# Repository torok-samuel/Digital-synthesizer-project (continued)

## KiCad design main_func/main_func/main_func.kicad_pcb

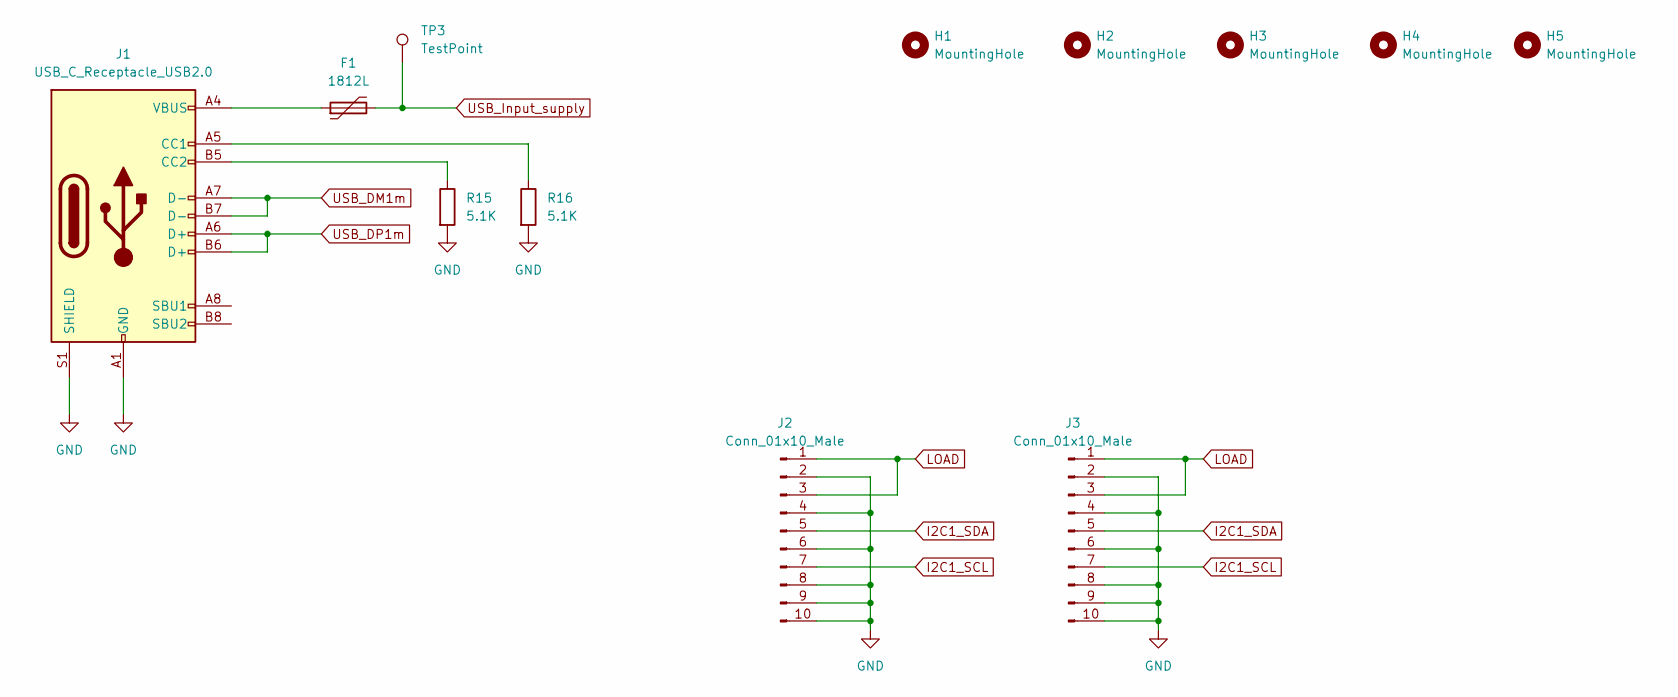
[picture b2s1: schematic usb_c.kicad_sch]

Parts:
F1: 1812L; FUSM4632X200N
H1, H2, H3, H4, H5: MountingHole; MountingHole_3.2mm_M3_Pad_Via
J1: USB_C_Receptacle_USB2.0; USB_C_Receptacle_HRO_TYPE-C-31-M-12
J2, J3: Conn_01x10_Male; IDC-Header_2x05_P2.54mm_Horizontal
R15, R16: 5.1K; R_0805_2012Metric_Pad1.20x1.40mm_HandSolder
TP3: TestPoint; TestPoint_Keystone_5010-5014_Multipurpose

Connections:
GND: J1.A1 (GND), J1.A12 (GND), J1.B1 (GND), J1.B12 (GND), J1.S1 (SHIELD), J2.2, J2.4, J2.6, J2.8, J2.9, J2.10, J3.2, J3.4, J3.6, J3.8, J3.9, J3.10, R15.2, R16.2; also elsewhere on the board
I2C1_SCL: J2.7, J3.7; also elsewhere on the board
I2C1_SDA: J2.5, J3.5; also elsewhere on the board
LOAD: J2.1, J2.3, J3.1, J3.3; also elsewhere on the board
unnamed: F1.1, J1.A4 (VBUS), J1.A9 (VBUS), J1.B4 (VBUS), J1.B9 (VBUS)
unnamed: J1.A5 (CC1), R16.1
unnamed: J1.B5 (CC2), R15.1
USB_DM1m: J1.A7 (D-), J1.B7 (D-); also elsewhere on the board
USB_DP1m: J1.A6 (D+), J1.B6 (D+); also elsewhere on the board
USB_Input_supply: F1.2, TP3.1; also elsewhere on the board

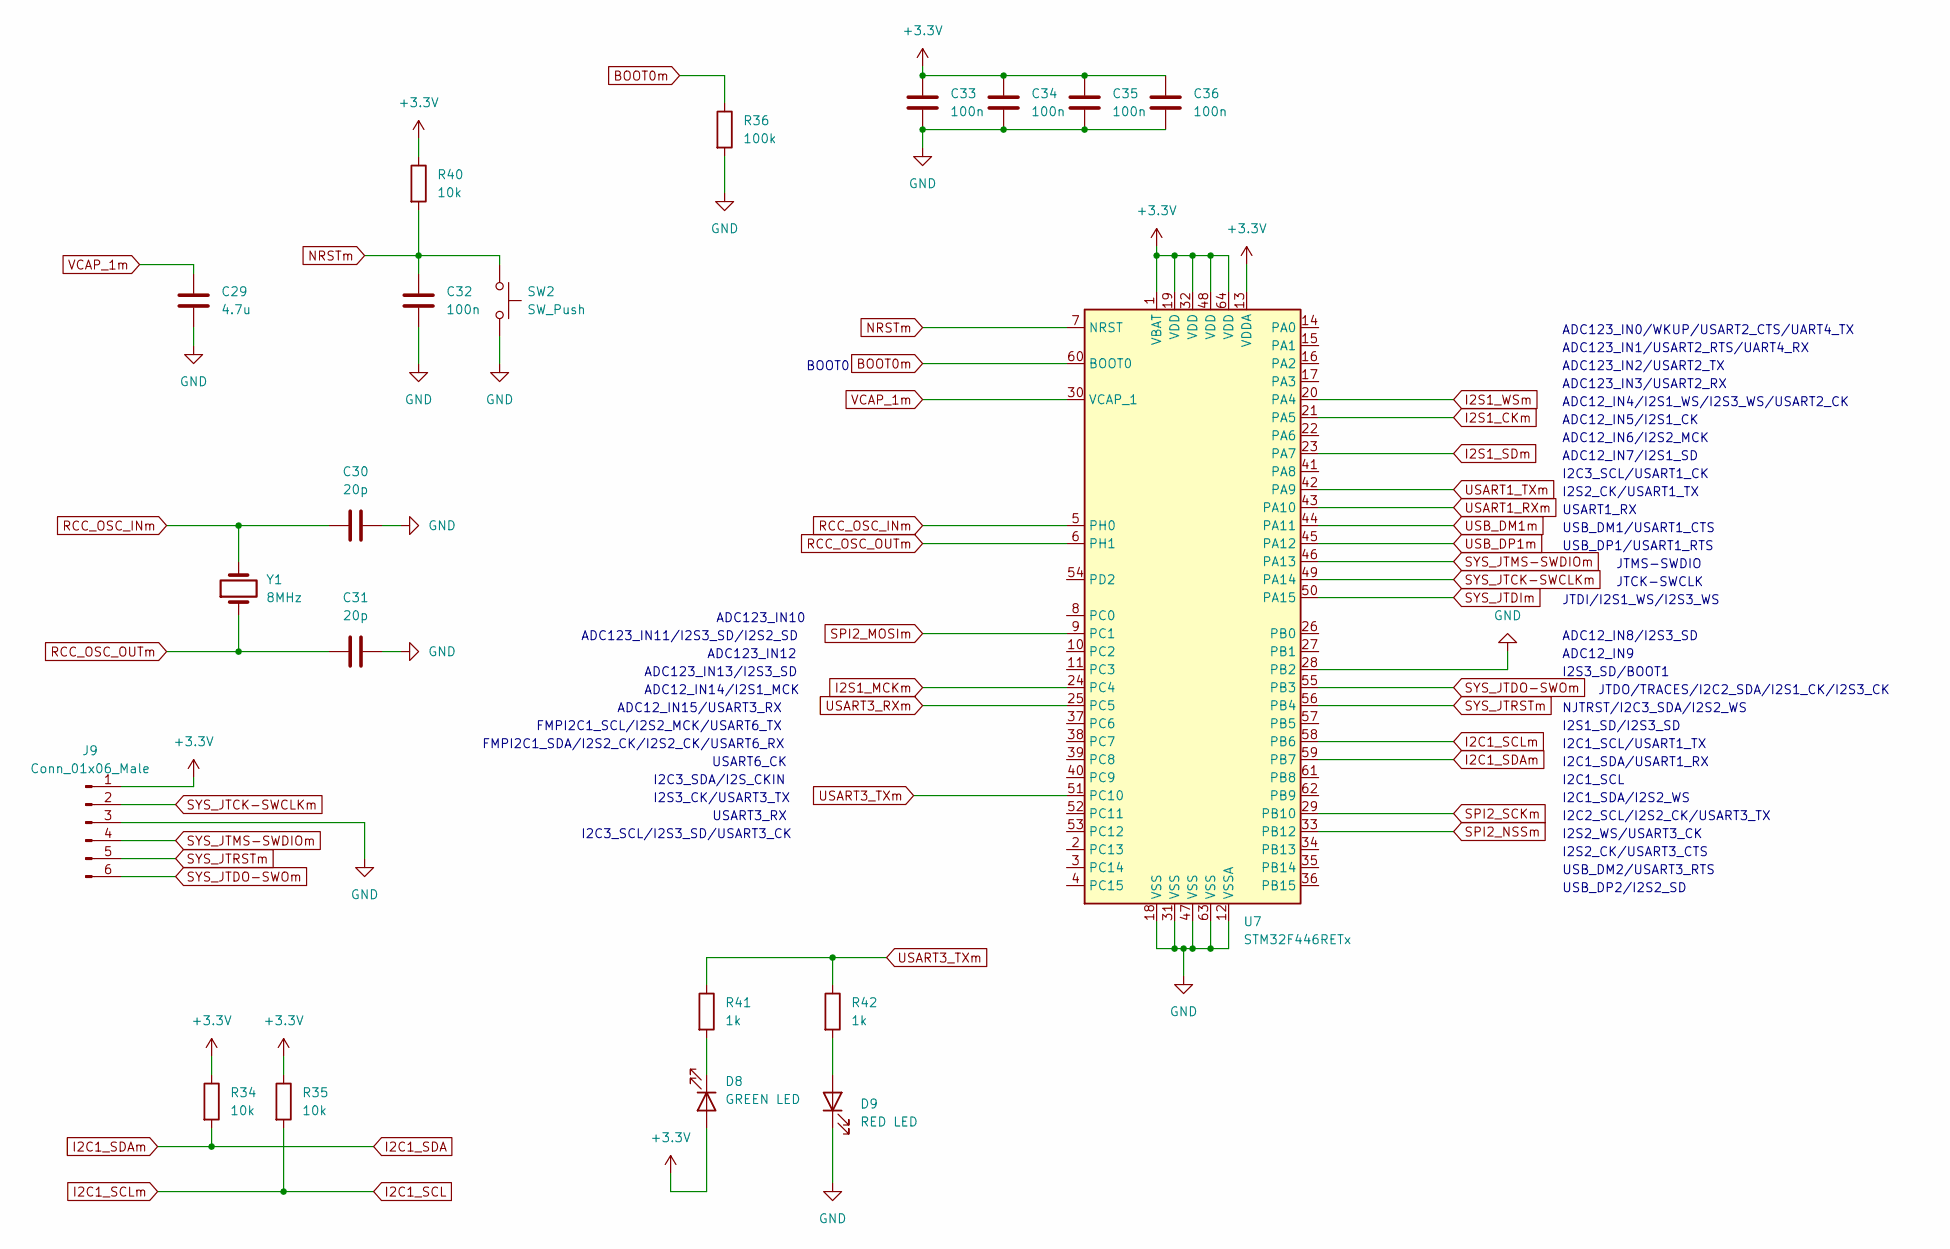
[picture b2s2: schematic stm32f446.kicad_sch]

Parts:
C29: 4.7u; C_0805_2012Metric_Pad1.18x1.45mm_HandSolder
C30, C31: 20p; C_0805_2012Metric_Pad1.18x1.45mm_HandSolder
C32, C33, C34, C35, C36: 100n; C_0805_2012Metric_Pad1.18x1.45mm_HandSolder
D8: GREEN LED; LED_0805_2012Metric_Pad1.15x1.40mm_HandSolder
D9: RED LED; LED_0805_2012Metric_Pad1.15x1.40mm_HandSolder
J9: Conn_01x06_Male; PinSocket_1x06_P2.54mm_Horizontal
R34, R35, R40: 10k; R_0805_2012Metric_Pad1.20x1.40mm_HandSolder
R36: 100k; R_0805_2012Metric_Pad1.20x1.40mm_HandSolder
R41, R42: 1k; R_0805_2012Metric_Pad1.20x1.40mm_HandSolder
SW2: SW_Push; ROCPU Switches TP10721645
U7: STM32F446RETx; LQFP-64_10x10mm_P0.5mm
Y1: 8MHz; Crystal_SMD_HC49-SD_HandSoldering

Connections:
+3V3: C33.1, C34.1, C35.1, C36.1, D8.2 (A), J9.1, R34.1, R35.1, R40.1, U7.1 (VBAT), U7.13 (VDDA), U7.19 (VDD), U7.32 (VDD), U7.48 (VDD), U7.64 (VDD); also elsewhere on the board
BCLKda: U7.21 (PA5); also elsewhere on the board
BOOT0m: R36.1, U7.60 (BOOT0)
DATAda: U7.23 (PA7); also elsewhere on the board
GND: C29.2, C30.2, C31.2, C32.2, C33.2, C34.2, C35.2, C36.2, D9.1 (K), J9.3, R36.2, SW2.2, U7.12 (VSSA), U7.18 (VSS), U7.28 (PB2), U7.31 (VSS), U7.47 (VSS), U7.63 (VSS); also elsewhere on the board
I2C1_SCL: R35.2, U7.58 (PB6); also elsewhere on the board
I2C1_SDA: R34.2, U7.59 (PB7); also elsewhere on the board
I2S1_MCKm: U7.24 (PC4); also elsewhere on the board
I2S1_WSm: U7.20 (PA4); also elsewhere on the board
MCda: U7.29 (PB10); also elsewhere on the board
MDda: U7.9 (PC1); also elsewhere on the board
MLda: U7.33 (PB12); also elsewhere on the board
NRSTm: C32.1, R40.2, SW2.1, U7.7 (NRST)
unnamed: D8.1 (K), R41.2
unnamed: D9.2 (A), R42.2
RCC_OSC_INm: C30.1, U7.5 (PH0), Y1.2
RCC_OSC_OUTm: C31.1, U7.6 (PH1), Y1.1
SYS_JTCK-SWCLKm: J9.2, U7.49 (PA14)
SYS_JTDIm: U7.50 (PA15)
SYS_JTDO-SWOm: J9.6, U7.55 (PB3)
SYS_JTMS-SWDIOm: J9.4, U7.46 (PA13)
SYS_JTRSTm: J9.5, U7.56 (PB4)
USART1_RXm: U7.43 (PA10); also elsewhere on the board
USART1_TXm: U7.42 (PA9); also elsewhere on the board
USART3_RXm: U7.25 (PC5)
USART3_TXm: R41.1, R42.1, U7.51 (PC10)
USB_DM1m: U7.44 (PA11); also elsewhere on the board
USB_DP1m: U7.45 (PA12); also elsewhere on the board
VCAP_1m: C29.1, U7.30 (VCAP_1)

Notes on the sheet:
ADC123_IN3/USART2_RX
I2S2_CK/USART3_CTS
FMPI2C1_SDA/I2S2_CK/I2S2_CK/USART6_RX
ADC12_IN4/I2S1_WS/I2S3_WS/USART2_CK
USB_DP2/I2S2_SD
I2C1_SCL
I2C1_SDA/USART1_RX
ADC12_IN7/I2S1_SD
ADC123_IN12
USART1_RX
FMPI2C1_SCL/I2S2_MCK/USART6_TX
I2C3_SDA/I2S_CKIN
I2C1_SCL/USART1_TX
USART6_CK
ADC123_IN0/WKUP/USART2_CTS/UART4_TX
I2S2_WS/USART3_CK
JTCK-SWCLK
JTMS-SWDIO
I2C3_SCL/USART1_CK
ADC123_IN10
NJTRST/I2C3_SDA/I2S2_WS
ADC123_IN2/USART2_TX
USB_DM1/USART1_CTS
I2C1_SDA/I2S2_WS
BOOT0
USART3_RX
ADC12_IN5/I2S1_CK
ADC12_IN14/I2S1_MCK
ADC123_IN13/I2S3_SD
ADC12_IN15/USART3_RX
I2C3_SCL/I2S3_SD/USART3_CK
ADC12_IN8/I2S3_SD
I2C2_SCL/I2S2_CK/USART3_TX
USB_DM2/USART3_RTS
ADC12_IN9
I2S3_CK/USART3_TX
ADC123_IN1/USART2_RTS/UART4_RX
JTDO/TRACES/I2C2_SDA/I2S1_CK/I2S3_CK
I2S1_SD/I2S3_SD
I2S3_SD/BOOT1

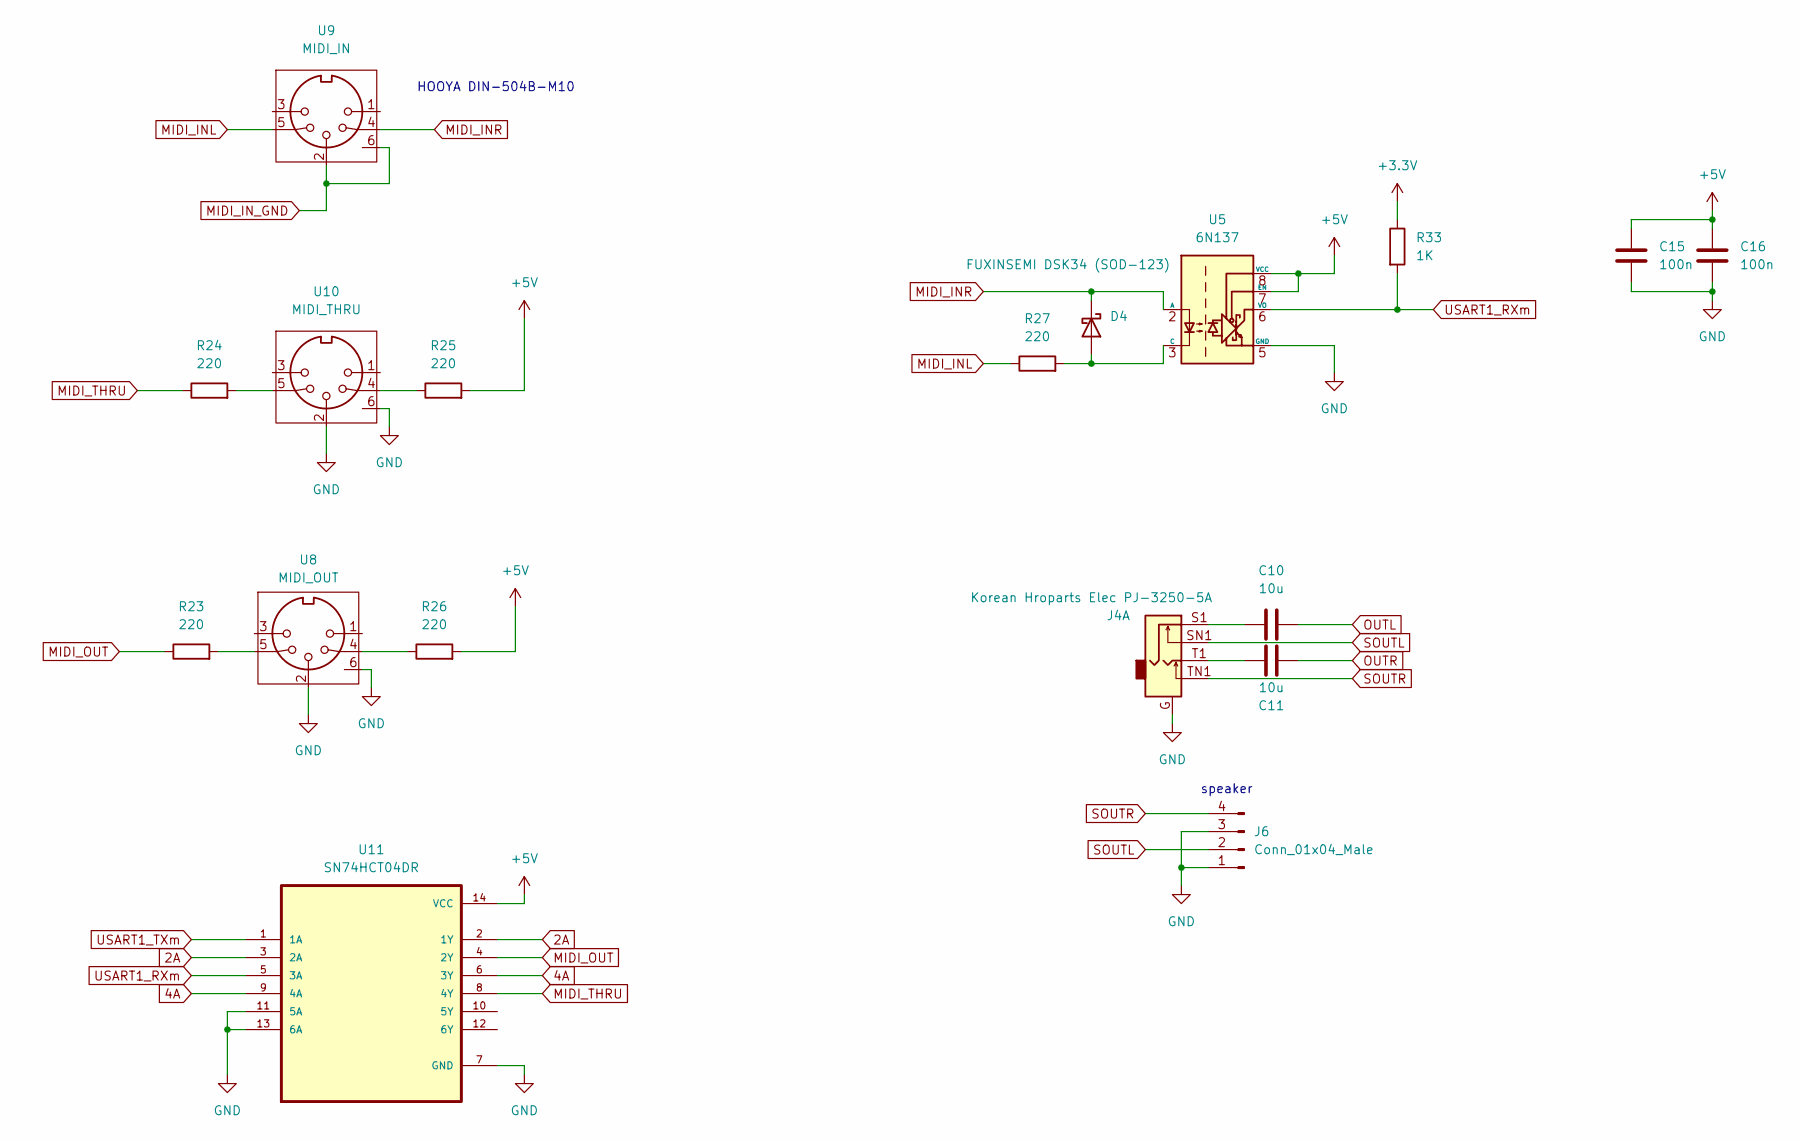
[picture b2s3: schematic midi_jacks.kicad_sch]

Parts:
C10, C11: 10u; C_Rect_L33.0mm_W15.0mm_P27.50mm_MKS4
C15, C16: 100n; C_0805_2012Metric_Pad1.18x1.45mm_HandSolder
D4: FUXINSEMI DSK34 (SOD-123); D_SOD-123
J4: Korean Hroparts Elec PJ-3250-5A
J6: Conn_01x04_Male; PinHeader_1x04_P2.54mm_Vertical
R23, R24, R25, R26, R27: 220; R_0805_2012Metric_Pad1.20x1.40mm_HandSolder
R33: 1K; R_0805_2012Metric_Pad1.20x1.40mm_HandSolder
U5: 6N137; DIP-8_W7.62mm
U8: MIDI_OUT; midi_7pin
U9: MIDI_IN; midi_7pin
U10: MIDI_THRU; midi_7pin
U11: SN74HCT04DR; SOIC-14_3.9x8.7mm_P1.27mm

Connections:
2A: U11.2 (1Y), U11.3 (2A)
4A: U11.6 (3Y), U11.9 (4A)
+3V3: R33.1; also elsewhere on the board
+5V: C15.1, C16.1, R25.2, R26.2, U5.7 (EN), U5.8 (VCC), U11.14 (VCC); also elsewhere on the board
GND: C15.2, C16.2, J4.G, J6.1, J6.3, U5.5 (GND), U8.2, U8.6, U10.2, U10.6, U11.7 (GND), U11.11 (5A), U11.13 (6A); also elsewhere on the board
MIDI_INL: R27.1, U9.5
MIDI_INR: D4.1 (K), U5.2 (A), U9.4
MIDI_IN_GND: U9.2, U9.6
MIDI_OUT: R23.1, U11.4 (2Y)
MIDI_THRU: R24.1, U11.8 (4Y)
unnamed: C10.1, J4.S1
unnamed: C11.1, J4.T1
unnamed: D4.2 (A), R27.2, U5.3 (C)
unnamed: R23.2, U8.5
unnamed: R24.2, U10.5
unnamed: R25.1, U10.4
unnamed: R26.1, U8.4
OUTL: C10.2; also elsewhere on the board
OUTR: C11.2; also elsewhere on the board
SOUTL: J4.SN1, J6.2
SOUTR: J4.TN1, J6.4
USART1_RXm: R33.2, U5.6 (VO), U11.5 (3A); also elsewhere on the board
USART1_TXm: U11.1 (1A); also elsewhere on the board

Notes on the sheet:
speaker
HOOYA DIN-504B-M10

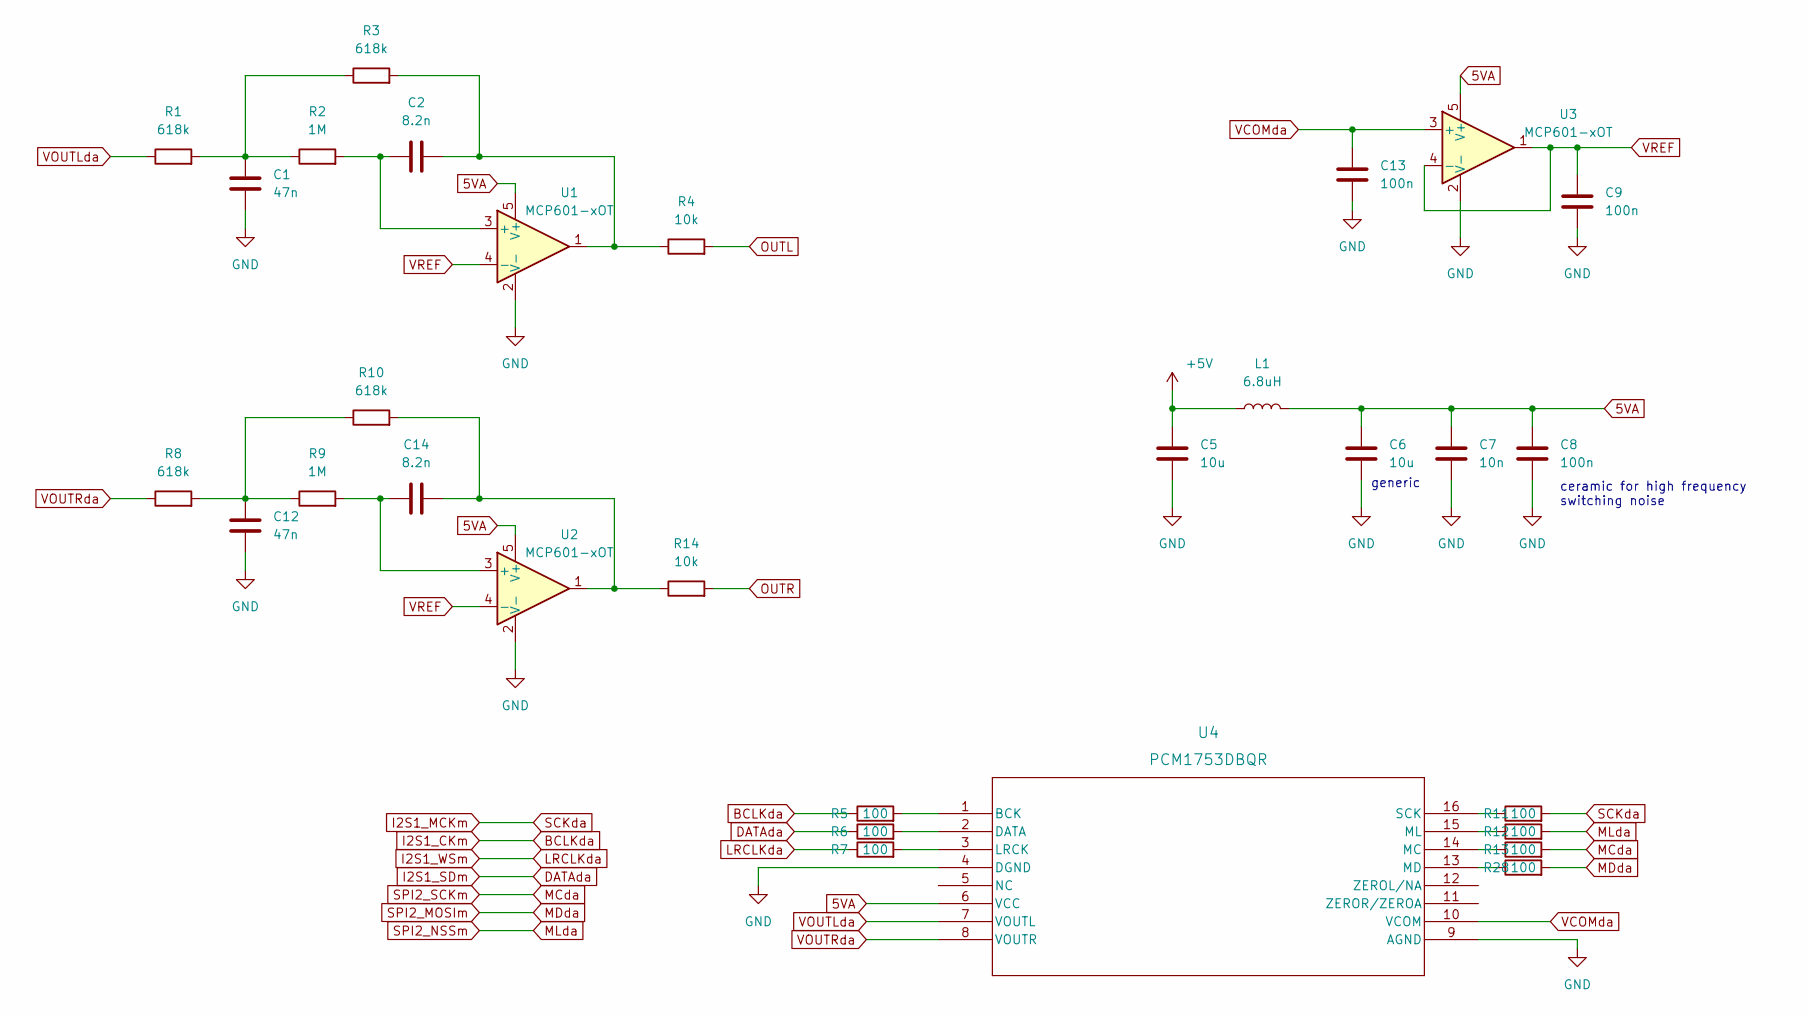
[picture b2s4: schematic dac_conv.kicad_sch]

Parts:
C1, C12: 47n; C_0805_2012Metric_Pad1.18x1.45mm_HandSolder
C2, C14: 8.2n; C_0805_2012Metric_Pad1.18x1.45mm_HandSolder
C5, C6: 10u; C_0805_2012Metric_Pad1.18x1.45mm_HandSolder
C7: 10n; C_0805_2012Metric_Pad1.18x1.45mm_HandSolder
C8, C9, C13: 100n; C_0805_2012Metric_Pad1.18x1.45mm_HandSolder
L1: 6.8uH; inductor_koherelec
R1, R3, R8, R10: 618k; R_0805_2012Metric_Pad1.20x1.40mm_HandSolder
R2, R9: 1M; R_0805_2012Metric_Pad1.20x1.40mm_HandSolder
R4, R14: 10k; R_0805_2012Metric_Pad1.20x1.40mm_HandSolder
R5, R6, R7, R11, R12, R13, R28: 100; R_0805_2012Metric_Pad1.20x1.40mm_HandSolder
U1, U2, U3: MCP601-xOT; SOT-23-5
U4: PCM1753DBQR; DBQ16

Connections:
5VA: C6.1, C7.1, C8.1, L1.2, U1.5 (V+), U2.5 (V+), U3.5 (V+), U4.6 (VCC)
+5V: C5.1, L1.1; also elsewhere on the board
BCLKda: R5.1; also elsewhere on the board
DATAda: R6.1; also elsewhere on the board
GND: C1.2, C5.2, C6.2, C7.2, C8.2, C9.2, C12.2, C13.2, U1.2 (V-), U2.2 (V-), U3.2 (V-), U4.4 (DGND), U4.9 (AGND); also elsewhere on the board
I2S1_MCKm: R11.2; also elsewhere on the board
I2S1_WSm: R7.1; also elsewhere on the board
MCda: R13.2; also elsewhere on the board
MDda: R28.2; also elsewhere on the board
MLda: R12.2; also elsewhere on the board
unnamed: C1.1, R1.2, R2.1, R3.1
unnamed: C2.1, R2.2, U1.3 (+)
unnamed: C2.2, R3.2, R4.1, U1.1
unnamed: C12.1, R8.2, R9.1, R10.1
unnamed: C14.1, R9.2, U2.3 (+)
unnamed: C14.2, R10.2, R14.1, U2.1
unnamed: R5.2, U4.1 (BCK)
unnamed: R6.2, U4.2 (DATA)
unnamed: R7.2, U4.3 (LRCK)
unnamed: R11.1, U4.16 (SCK)
unnamed: R12.1, U4.15 (ML)
unnamed: R13.1, U4.14 (MC)
unnamed: R28.1, U4.13 (MD)
OUTL: R4.2; also elsewhere on the board
OUTR: R14.2; also elsewhere on the board
VCOMda: C13.1, U3.3 (+), U4.10 (VCOM)
VOUTLda: R1.1, U4.7 (VOUTL)
VOUTRda: R8.1, U4.8 (VOUTR)
VREF: C9.1, U1.4 (-), U2.4 (-), U3.1, U3.4 (-)

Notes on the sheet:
generic
ceramic for high frequency switching noise

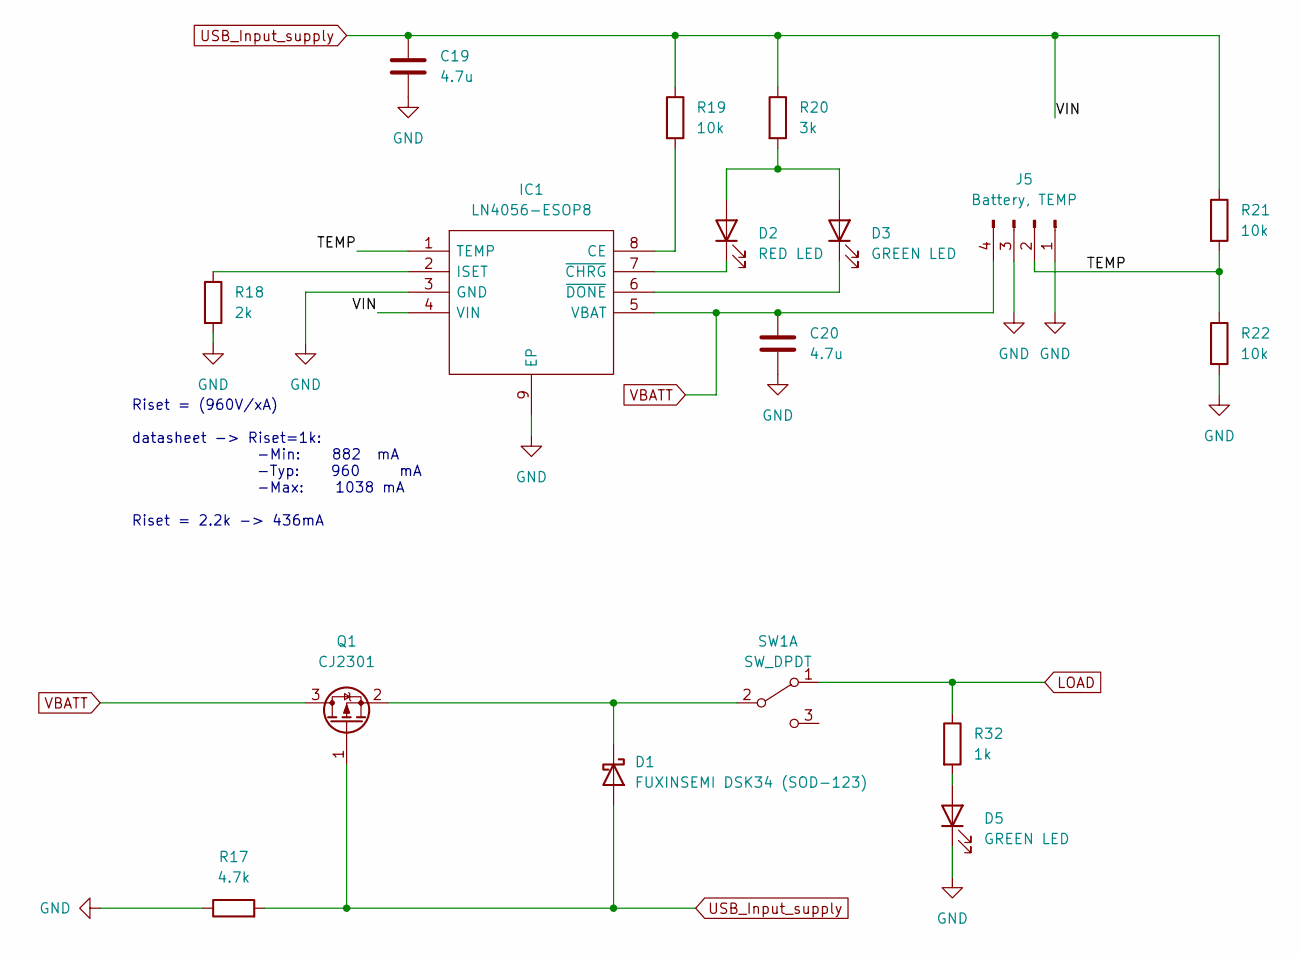
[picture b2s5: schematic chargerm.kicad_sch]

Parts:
C19, C20: 4.7u; C_0805_2012Metric_Pad1.18x1.45mm_HandSolder
D1: FUXINSEMI DSK34 (SOD-123); D_SOD-123
D2: RED LED; LED_0805_2012Metric_Pad1.15x1.40mm_HandSolder
D3, D5: GREEN LED; LED_0805_2012Metric_Pad1.15x1.40mm_HandSolder
IC1: LN4056-ESOP8; SOIC127P600X175-9N; Manufacturer_Part_Number TP4056-42-ESOP8
J5: Battery, TEMP; PinHeader_1x04_P2.54mm_Horizontal
Q1: CJ2301; SOT-23_Handsoldering
R17: 4.7k; R_0805_2012Metric_Pad1.20x1.40mm_HandSolder
R18: 2k; R_0805_2012Metric_Pad1.20x1.40mm_HandSolder
R19, R21, R22: 10k; R_0805_2012Metric_Pad1.20x1.40mm_HandSolder
R20: 3k; R_0805_2012Metric_Pad1.20x1.40mm_HandSolder
R32: 1k; R_0805_2012Metric_Pad1.20x1.40mm_HandSolder
SW1: SW_DPDT; PinHeader_1x03_P2.54mm_Horizontal

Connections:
/Power_dcdc/Battery_chargerm/TEMP: IC1.1 (TEMP), J5.2, R21.2, R22.1
GND: C19.2, C20.2, D5.1 (K), IC1.3 (GND), IC1.9 (EP), J5.1, J5.3, R17.1, R18.2, R22.2; also elsewhere on the board
LOAD: R32.1, SW1.1 (A); also elsewhere on the board
unnamed: D1.1 (K), Q1.2 (S), SW1.2 (B)
unnamed: D2.1 (K), IC1.7 (~CHRG)
unnamed: D2.2 (A), D3.2 (A), R20.2
unnamed: D3.1 (K), IC1.6 (~DONE)
unnamed: D5.2 (A), R32.2
unnamed: IC1.2 (ISET), R18.1
unnamed: IC1.8 (CE), R19.2
USB_Input_supply: C19.1, D1.2 (A), IC1.4 (VIN), Q1.1 (G), R17.2, R19.1, R20.1, R21.1; also elsewhere on the board
VBATT: C20.1, IC1.5 (VBAT), J5.4, Q1.3 (D)

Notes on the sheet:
Riset = (960V/xA) datasheet -> Riset=1k: -Min: 882 mA -Typ: 960 mA -Max: 1038 mA Riset = 2.2k -> 436mA

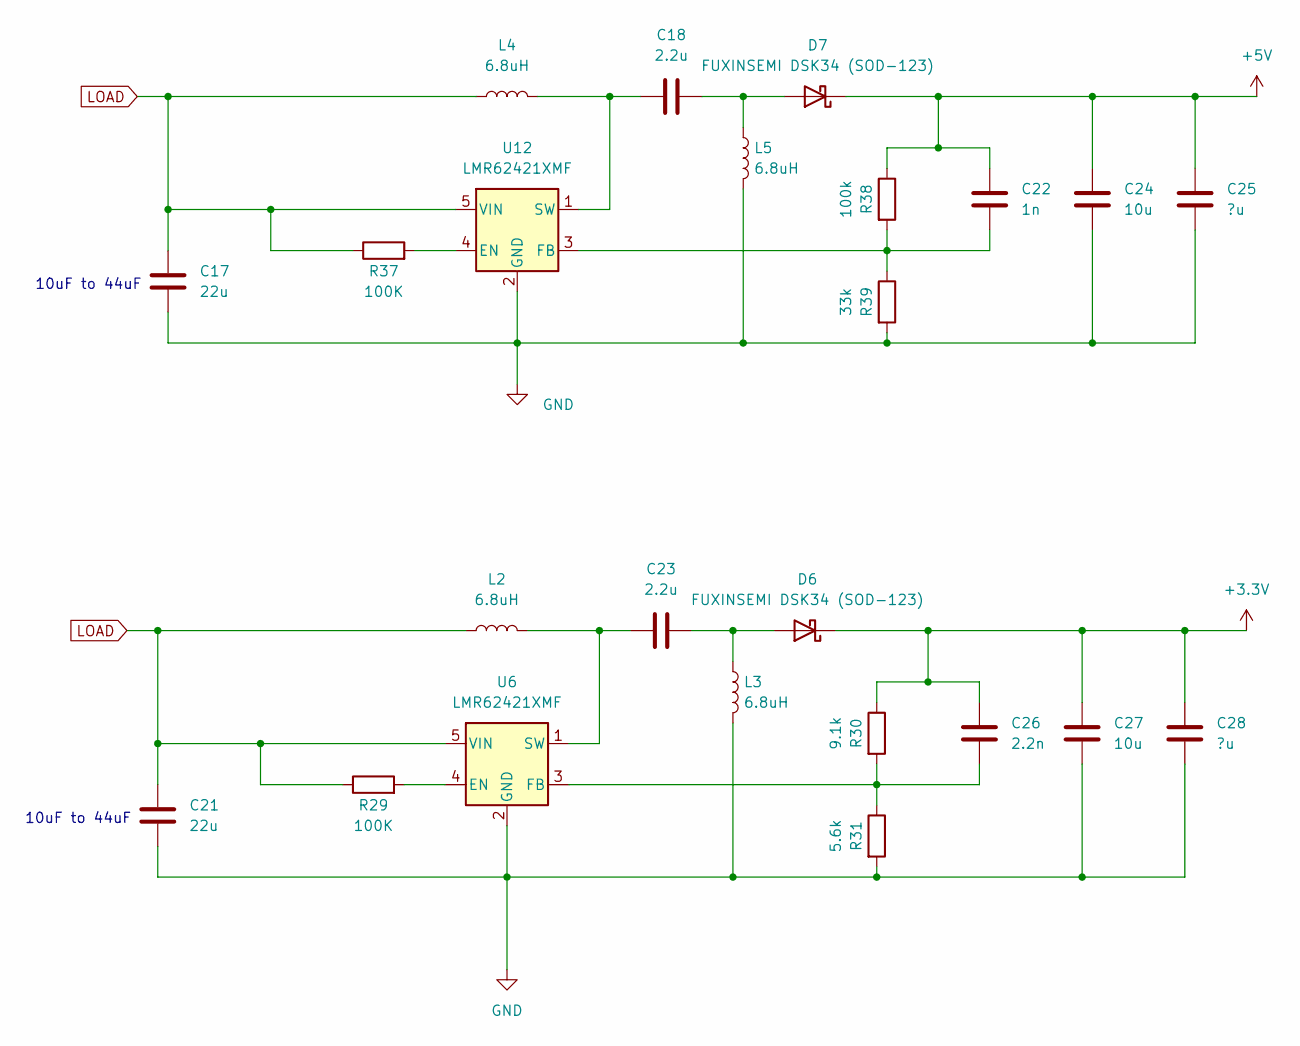
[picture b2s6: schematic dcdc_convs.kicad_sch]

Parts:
C17, C21: 22u; C_0805_2012Metric_Pad1.18x1.45mm_HandSolder
C18, C23: 2.2u; C_0805_2012Metric_Pad1.18x1.45mm_HandSolder
C22: 1n; C_0805_2012Metric_Pad1.18x1.45mm_HandSolder
C24, C27: 10u; C_0805_2012Metric_Pad1.18x1.45mm_HandSolder
C25, C28: ?u; C_0805_2012Metric_Pad1.18x1.45mm_HandSolder
C26: 2.2n; C_0805_2012Metric_Pad1.18x1.45mm_HandSolder
D6, D7: FUXINSEMI DSK34 (SOD-123); D_SOD-123
L2, L3, L4, L5: 6.8uH; inductor_koherelec
R29, R37: 100K; R_0805_2012Metric_Pad1.20x1.40mm_HandSolder
R30: 9.1k; R_0805_2012Metric_Pad1.20x1.40mm_HandSolder
R31: 5.6k; R_0805_2012Metric_Pad1.20x1.40mm_HandSolder
R38: 100k; R_0805_2012Metric_Pad1.20x1.40mm_HandSolder
R39: 33k; R_0805_2012Metric_Pad1.20x1.40mm_HandSolder
U6, U12: LMR62421XMF; SOT-23-5

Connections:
+3V3: C26.1, C27.1, C28.1, D6.1 (K), R30.1; also elsewhere on the board
+5V: C22.1, C24.1, C25.1, D7.1 (K), R38.1; also elsewhere on the board
GND: C17.2, C21.2, C24.2, C25.2, C27.2, C28.2, L3.2, L5.2, R31.2, R39.2, U6.2 (GND), U12.2 (GND); also elsewhere on the board
LOAD: C17.1, C21.1, L2.1, L4.1, R29.1, R37.1, U6.5 (VIN), U12.5 (VIN); also elsewhere on the board
unnamed: C18.1, L4.2, U12.1 (SW)
unnamed: C18.2, D7.2 (A), L5.1
unnamed: C22.2, R38.2, R39.1, U12.3 (FB)
unnamed: C23.1, L2.2, U6.1 (SW)
unnamed: C23.2, D6.2 (A), L3.1
unnamed: C26.2, R30.2, R31.1, U6.3 (FB)
unnamed: R29.2, U6.4 (EN)
unnamed: R37.2, U12.4 (EN)

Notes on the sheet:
10uF to 44uF

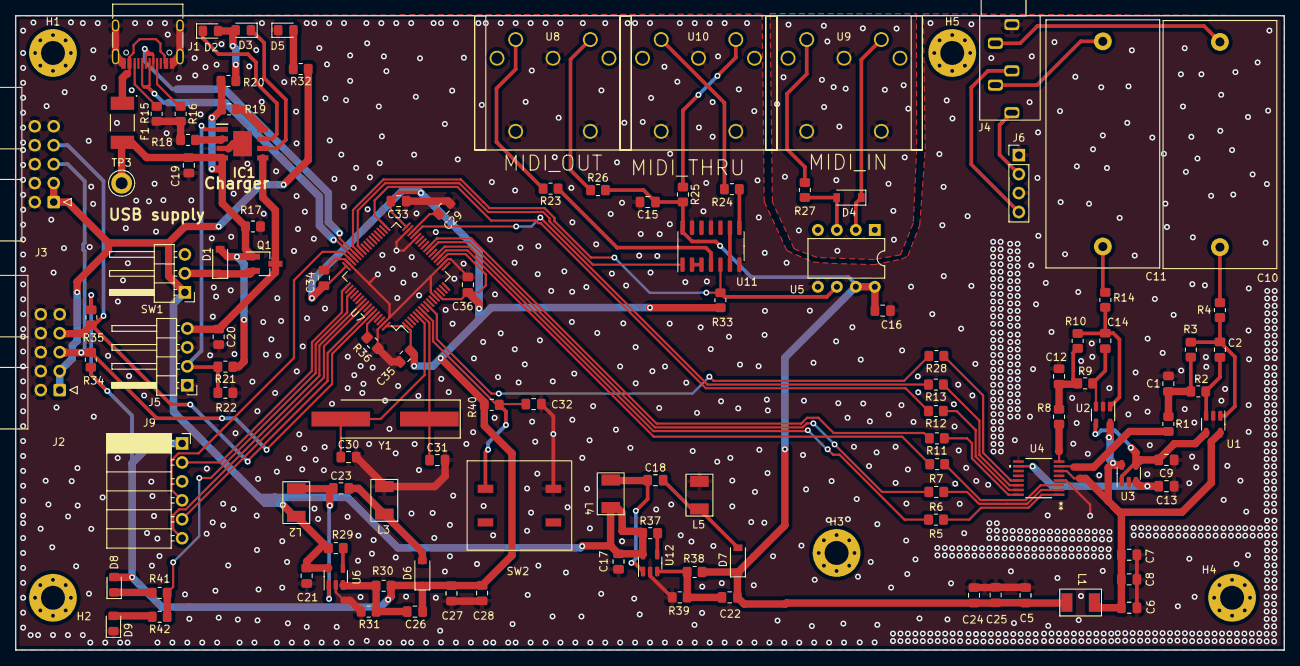
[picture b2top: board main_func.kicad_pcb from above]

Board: 2 copper layers, 170.0 x 85.0 mm, 121 parts (0 on the bottom side), 86 nets.

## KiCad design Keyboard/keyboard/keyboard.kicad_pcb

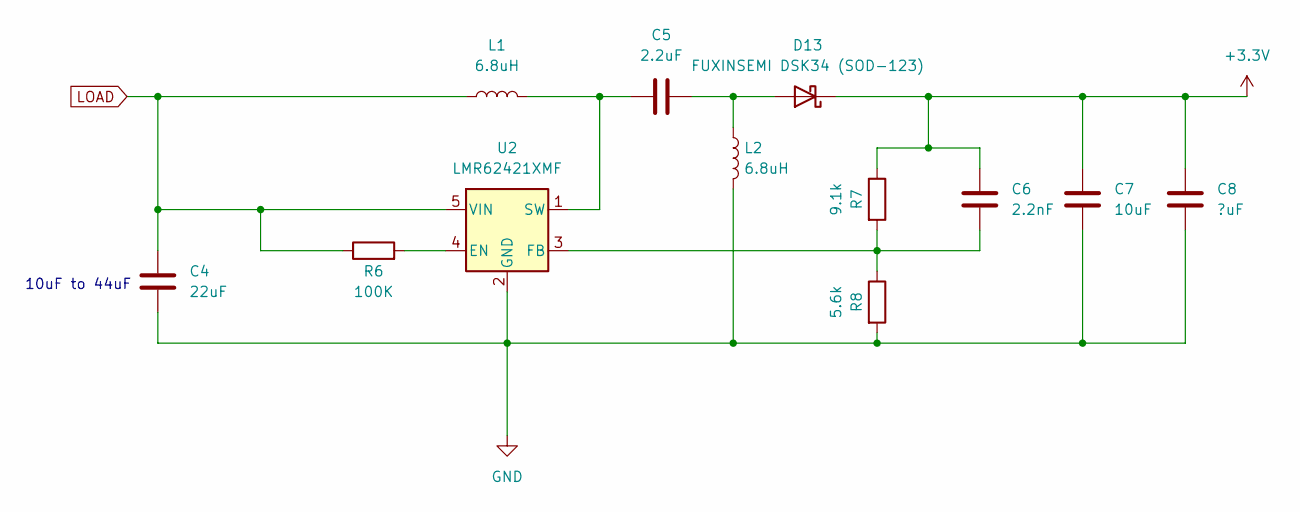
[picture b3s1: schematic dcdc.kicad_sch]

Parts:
C4: 22uF; C_0805_2012Metric_Pad1.18x1.45mm_HandSolder
C5: 2.2uF; C_0805_2012Metric_Pad1.18x1.45mm_HandSolder
C6: 2.2nF; C_0805_2012Metric_Pad1.18x1.45mm_HandSolder
C7: 10uF; C_0805_2012Metric_Pad1.18x1.45mm_HandSolder
C8: ?uF; C_0805_2012Metric_Pad1.18x1.45mm_HandSolder
D13: FUXINSEMI DSK34 (SOD-123); D_SOD-123
L1, L2: 6.8uH; inductor_koherelec
R6: 100K; R_0805_2012Metric_Pad1.20x1.40mm_HandSolder
R7: 9.1k; R_0805_2012Metric_Pad1.20x1.40mm_HandSolder
R8: 5.6k; R_0805_2012Metric_Pad1.20x1.40mm_HandSolder
U2: LMR62421XMF; SOT-23-5

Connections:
+3V3: C6.1, C7.1, C8.1, D13.1 (K), R7.1; also elsewhere on the board
GND: C4.2, C7.2, C8.2, L2.2, R8.2, U2.2 (GND); also elsewhere on the board
LOAD: C4.1, L1.1, R6.1, U2.5 (VIN); also elsewhere on the board
unnamed: C5.1, L1.2, U2.1 (SW)
unnamed: C5.2, D13.2 (A), L2.1
unnamed: C6.2, R7.2, R8.1, U2.3 (FB)
unnamed: R6.2, U2.4 (EN)

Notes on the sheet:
10uF to 44uF

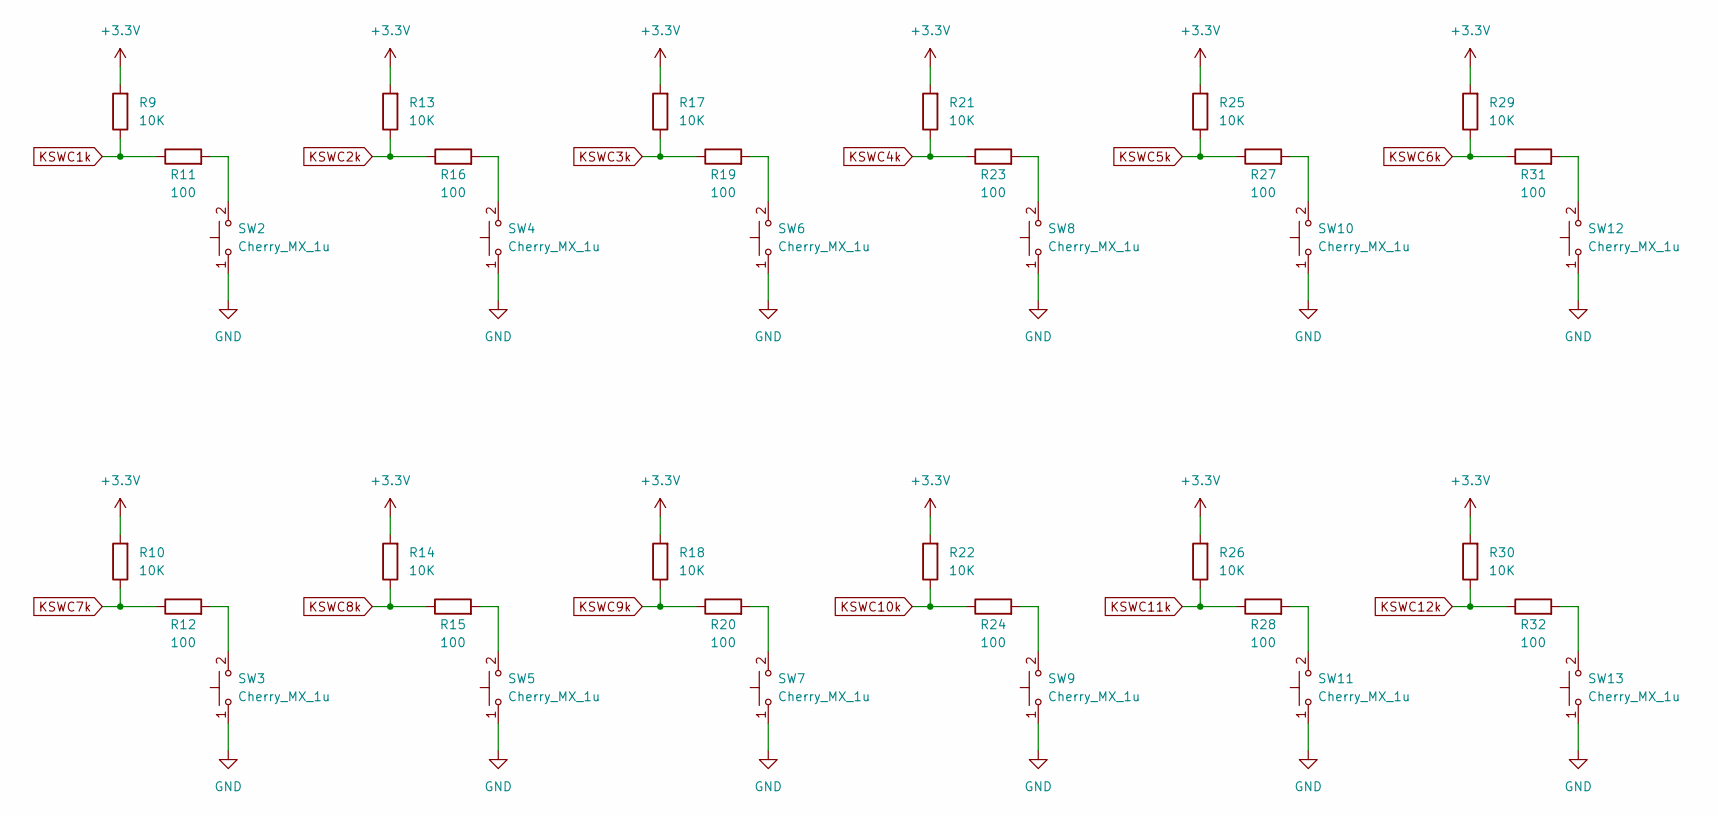
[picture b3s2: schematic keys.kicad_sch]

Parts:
R9, R10, R13, R14, R17, R18, R21, R22, R25, R26, R29, R30: 10K; R_0805_2012Metric_Pad1.20x1.40mm_HandSolder
R11, R12, R15, R16, R19, R20, R23, R24, R27, R28, R31, R32: 100; R_0805_2012Metric_Pad1.20x1.40mm_HandSolder
SW2, SW3, SW4, SW5, SW6, SW7, SW8, SW9, SW10, SW11, SW12, SW13: Cherry_MX_1u; SW_Cherry_MX_PCB_1.00u

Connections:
+3V3: R9.2, R10.2, R13.2, R14.2, R17.2, R18.2, R21.2, R22.2, R25.2, R26.2, R29.2, R30.2; also elsewhere on the board
GND: SW2.1, SW3.1, SW4.1, SW5.1, SW6.1, SW7.1, SW8.1, SW9.1, SW10.1, SW11.1, SW12.1, SW13.1; also elsewhere on the board
KSWC1k: R9.1, R11.1; also elsewhere on the board
KSWC2k: R13.1, R16.1; also elsewhere on the board
KSWC3k: R17.1, R19.1; also elsewhere on the board
KSWC4k: R21.1, R23.1; also elsewhere on the board
KSWC5k: R25.1, R27.1; also elsewhere on the board
KSWC6k: R29.1, R31.1; also elsewhere on the board
KSWC7k: R10.1, R12.1; also elsewhere on the board
KSWC8k: R14.1, R15.1; also elsewhere on the board
KSWC9k: R18.1, R20.1; also elsewhere on the board
KSWC10k: R22.1, R24.1; also elsewhere on the board
KSWC11k: R26.1, R28.1; also elsewhere on the board
KSWC12k: R30.1, R32.1; also elsewhere on the board
unnamed: R11.2, SW2.2
unnamed: R12.2, SW3.2
unnamed: R15.2, SW5.2
unnamed: R16.2, SW4.2
unnamed: R19.2, SW6.2
unnamed: R20.2, SW7.2
unnamed: R23.2, SW8.2
unnamed: R24.2, SW9.2
unnamed: R27.2, SW10.2
unnamed: R28.2, SW11.2
unnamed: R31.2, SW12.2
unnamed: R32.2, SW13.2
